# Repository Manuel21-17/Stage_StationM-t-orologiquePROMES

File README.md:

# Stage_StationM-t-orologiquePROMES
The following repository contains the various programs, CAD files, KiCad schematics, and applications developed as part of the project “CONCEPTION ET MISE EN SERVICE D’UNE PLATEFORME D’ADQUISITION DE DONNÉES MÉTÉOROLOGIQUES ET PHOTOVOLTAIQUES” during a 4-year internship as part of an engineering program.

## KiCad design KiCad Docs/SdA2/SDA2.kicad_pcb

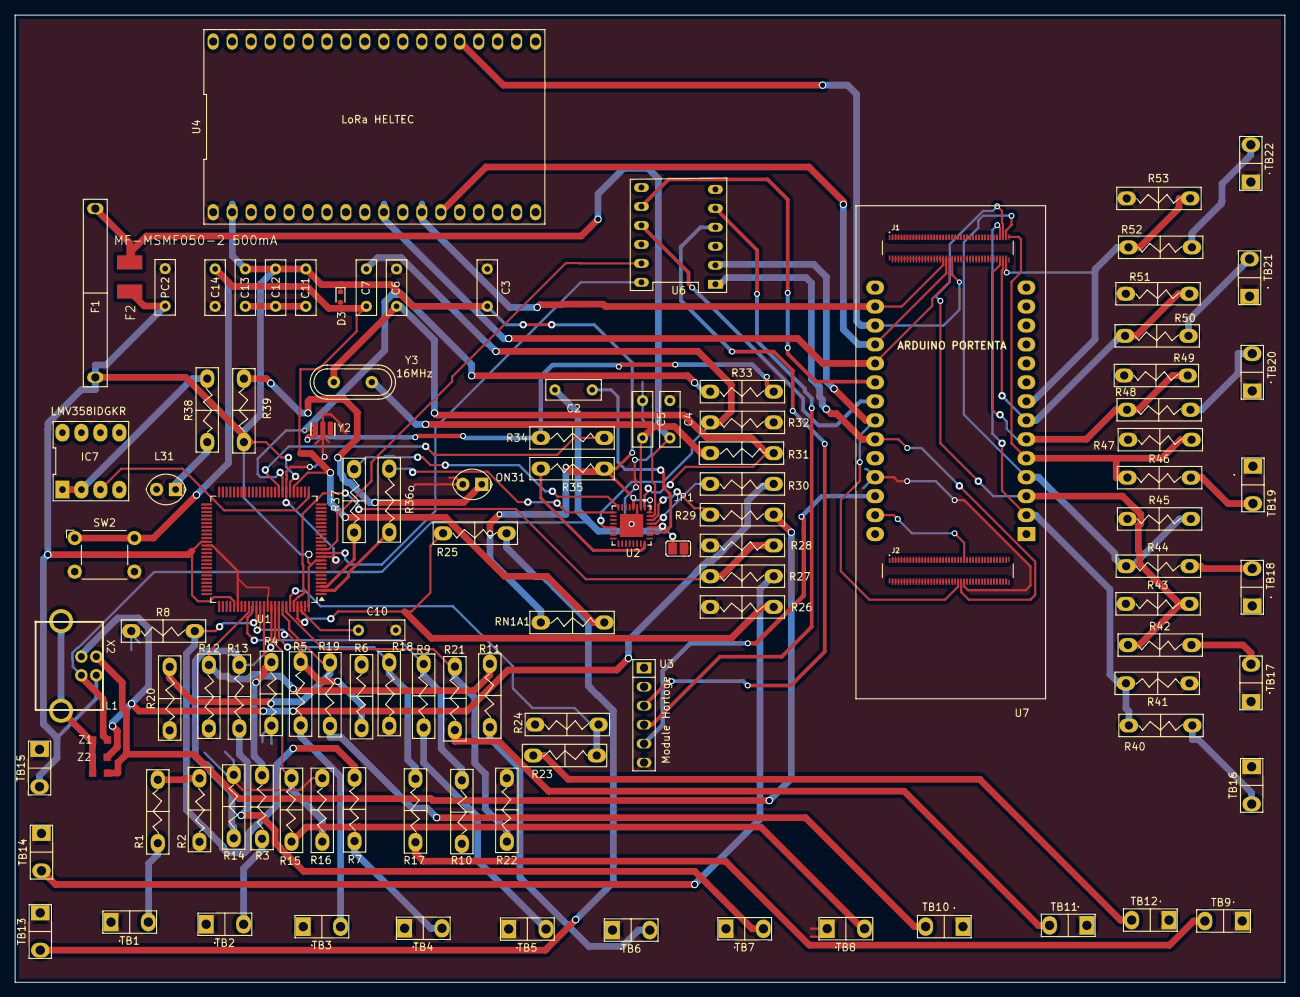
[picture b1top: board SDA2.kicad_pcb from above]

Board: 2 copper layers, 170.1 x 129.6 mm, 110 parts (0 on the bottom side), 81 nets.

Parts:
C2, C7: 1u; C_Rect_L7.2mm_W2.5mm_P5.00mm
C3, C4, C5, C6, C10, C11, C12, C13: 100n; C_Rect_L7.2mm_W2.5mm_P5.00mm
C14: 22p; C_Rect_L7.2mm_W2.5mm_P5.00mm
D3: 1N4148WT; D_SOD-523
F1: Fuse; Fussile
F2: MF-MSMF050-2 500mA; L1812
IC7: LMV358IDGKR; LM358N
J1, J2: DF40C-80DP-0.4V_51_; HRS_DF40C-80DP-0.4V_51_
JP1: SolderJumper_2_Open; OpenCircuit
L1: Z
L31: YELLOW; LED_Oval_W5.2mm_H3.8mm
ON31: GREEN; LED_Oval_W5.2mm_H3.8mm
PC2: 47u; C_Rect_L7.2mm_W2.5mm_P5.00mm
R1, R2, R3, R4, R5, R6, R7, R8, R9, R10, R11, R12, R13, R14, R15, R16, R17, R18, R19, R20, R21, R22, R23, R24, R25, R26, R27, R28, R29, R30, R31, R33, R34, R38, R39, R40, R41, R42, R43, R44, R45, R46, R47, R48, R49, R50, R51, R52, R53: R; RES
R32, R36, R37: 1K; RES
R35: 10k; RES
RN1A1: 10k; RES
SW2: SW_Omron_B3FS; SW_SPST_Omron_B3FS-100xP
TB1, TB2, TB3, TB4, TB5, TB6, TB7, TB8, TB9, TB10, TB11, TB12, TB13, TB14, TB15, TB16, TB17, TB18, TB19, TB20, TB21, TB22: TB2
U1: ATmega2560V-8A; TQFP-100_14x14mm_P0.5mm
U2: ATmega8U2-M; QFN-32-1EP_5x5mm_P0.5mm_EP3.1x3.1mm
U3: HORLOGE
U4: DIP-36_900_ELL
U6: Logic Shifter
U7: _REP_MODULE_ABX00042
X2: USB-B_TH; USB
Y2: 16MHz; HORLOGE1
Y3: CSTCE16; Horloge2
Z1, Z2: CG0603MLC-05E; Z

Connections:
+3.3V: U3.5 (VCC), U7.JD3 (+3.3)
+5V: C3.2, C11.1, C12.1, C13.1, D3.1 (K), F1.1, F2.2, PC2.1 (+), R35.2, R39.1, RN1A1.1, TB15.2, U1.10 (VCC), U1.31 (VCC), U1.61 (VCC), U1.80 (VCC), U1.100 (AVCC), U2.4 (VCC), U2.32 (AVCC), U4.2 (5V), U7.J1_32 (VIN), X2.1
/L13: IC7.1 (OUT), IC7.2 (-IN), R38.1
/PB7: IC7.3 (+IN), U1.26 (PB7)
CS_LORA: U4.12 (LoRa_CS), U7.J2_36 (D7)
EntCap1: R25.2, R26.1, U1.97 (PF0)
EntCap2: R27.2, R28.1, U1.96 (PF1)
GND: C3.1, C4.1, C5.1, C6.1, C10.2, C14.2, JP1.2 (B), L31.2, ON31.2, PC2.2 (-), R2.2, R4.2, R6.2, R8.2, R10.2, R12.2, R14.2, R16.2, R18.2, R20.2, R22.2, R24.2, R26.2, R28.2, R32.1, R41.2, R43.2, R45.2, R47.2, R49.2, R51.2, R53.2, SW2.2, TB1.1, TB2.1, TB3.1, TB4.1, TB5.1, TB6.1, TB7.1, TB8.1, TB9.1, TB10.1, TB11.1, TB12.1, TB13.1, TB14.1, TB15.1, TB16.1, TB17.1, TB18.1, TB19.1, TB20.1, TB21.1, TB22.1, U1.11 (GND), U1.32 (GND), U1.62 (GND), U1.81 (GND), U1.89 (PK0), U1.99 (GND), U2.3 (GND), U2.33 (GND), U3.6 (GND), U4.1 (GND), U7.J1_31 (GND), Y3.2
MISO: U4.10 (LoRa_MISO), U7.J2_40 (D10)
MOSI: U4.23 (LoRa_MOSI), U7.J2_42 (D8)
unnamed: C2.2, JP1.1 (A), L1.2, U2.28 (UGND), X2.4
unnamed: L1.1, X2.P$1, X2.P$2, Z1.1, Z2.1
unnamed: L31.1, R38.2
unnamed: ON31.1, R39.2
unnamed: R1.1, TB1.2
unnamed: R1.2, R2.1
unnamed: R3.1, TB2.2
unnamed: R5.1, TB3.2
unnamed: R7.1, TB4.2
unnamed: R9.1, TB5.2
unnamed: R11.1, TB6.2
unnamed: R13.1, TB7.2
unnamed: R15.1, TB8.2
unnamed: R17.1, TB9.2
unnamed: R19.1, TB10.2
unnamed: R21.1, TB11.2
unnamed: R23.1, TB12.2
unnamed: R25.1, TB13.2
unnamed: R27.1, TB14.2
unnamed: R29.1, X2.2, Z2.2
unnamed: R30.1, X2.3, Z1.2
unnamed: R33.1, R34.1, Y3.1
unnamed: R40.1, TB16.2
unnamed: R42.1, TB17.2
unnamed: R44.1, TB18.2
unnamed: R46.1, TB19.2
unnamed: R48.1, TB20.2
unnamed: R50.1, TB21.2
unnamed: R52.1, TB22.2
unnamed: C11.2, C12.2, C13.2
unnamed: C10.1, U1.98 (AREF)
unnamed: R23.2, R24.1, U1.95 (PF2)
unnamed: R21.2, R22.1, U1.94 (PF3)
unnamed: R19.2, R20.1, U1.93 (PF4)
unnamed: R17.2, R18.1, U1.92 (PF5)
unnamed: R15.2, R16.1, U1.91 (PF6)
unnamed: R13.2, R14.1, U1.90 (PF7)
unnamed: R3.2, R4.1, U1.88 (PK1)
unnamed: R5.2, R6.1, U1.87 (PK2)
unnamed: R7.2, R8.1, U1.86 (PK3)
unnamed: R9.2, R10.1, U1.85 (PK4)
unnamed: R11.2, R12.1, U1.84 (PK5)
unnamed: R34.2, U1.34 (XTAL1)
unnamed: R33.2, U1.33 (XTAL2), Y3.3
unnamed: R30.2, U2.29 (D+)
unnamed: R29.2, U2.30 (D-)
unnamed: C5.2, R31.1, U2.2 (PC0/XTAL2), Y2.1
unnamed: R35.1, U2.24 (PC1/~RESET)
unnamed: R37.1, U2.8 (PD2)
unnamed: R36.1, U2.9 (PD3)
unnamed: C2.1, U2.27 (UCAP)
unnamed: C4.2, F1.2, F2.1, U2.31 (UVCC)
unnamed: C6.2, R31.2, U2.1 (XTAL1), Y2.2
unnamed: C7.1, R32.2, U2.13 (~HWB/PD7)
unnamed: R40.2, R41.1, U7.J2_73 (A0)
unnamed: R42.2, R43.1, U7.J2_75 (A1)
unnamed: R44.2, R45.1, U7.J2_77 (A2)
unnamed: R46.2, R47.1, U7.J2_79 (A3)
unnamed: R48.2, R49.1, U7.J2_74 (A4)
unnamed: R50.2, R51.1, U7.J2_76 (A5/D20)
unnamed: R52.2, R53.1, U7.J2_78 (A6/D21)
PE0: R36.2, U1.2 (PE0)
PE1: R37.2, U1.3 (PE1)
PH0: U1.12 (PH0), U6.12 (HL1)
PH1: U1.13 (PH1), U6.11 (HL2)
RESET: C7.2, C14.1, D3.2 (A), RN1A1.2, SW2.1, U1.30 (~RESET)
RX_AP: U6.2 (LV2), U7.J1_35 (D13)
SCK: U4.13 (LoRa_SCLK), U7.J2_38 (D9)
SCLC: U3.3 (SCL), U7.J1_46 (D12)
SDAC: U3.4 (SDA), U7.J1_44 (D11)
TX_AP: U6.1 (LV1), U7.J1_33 (D14)

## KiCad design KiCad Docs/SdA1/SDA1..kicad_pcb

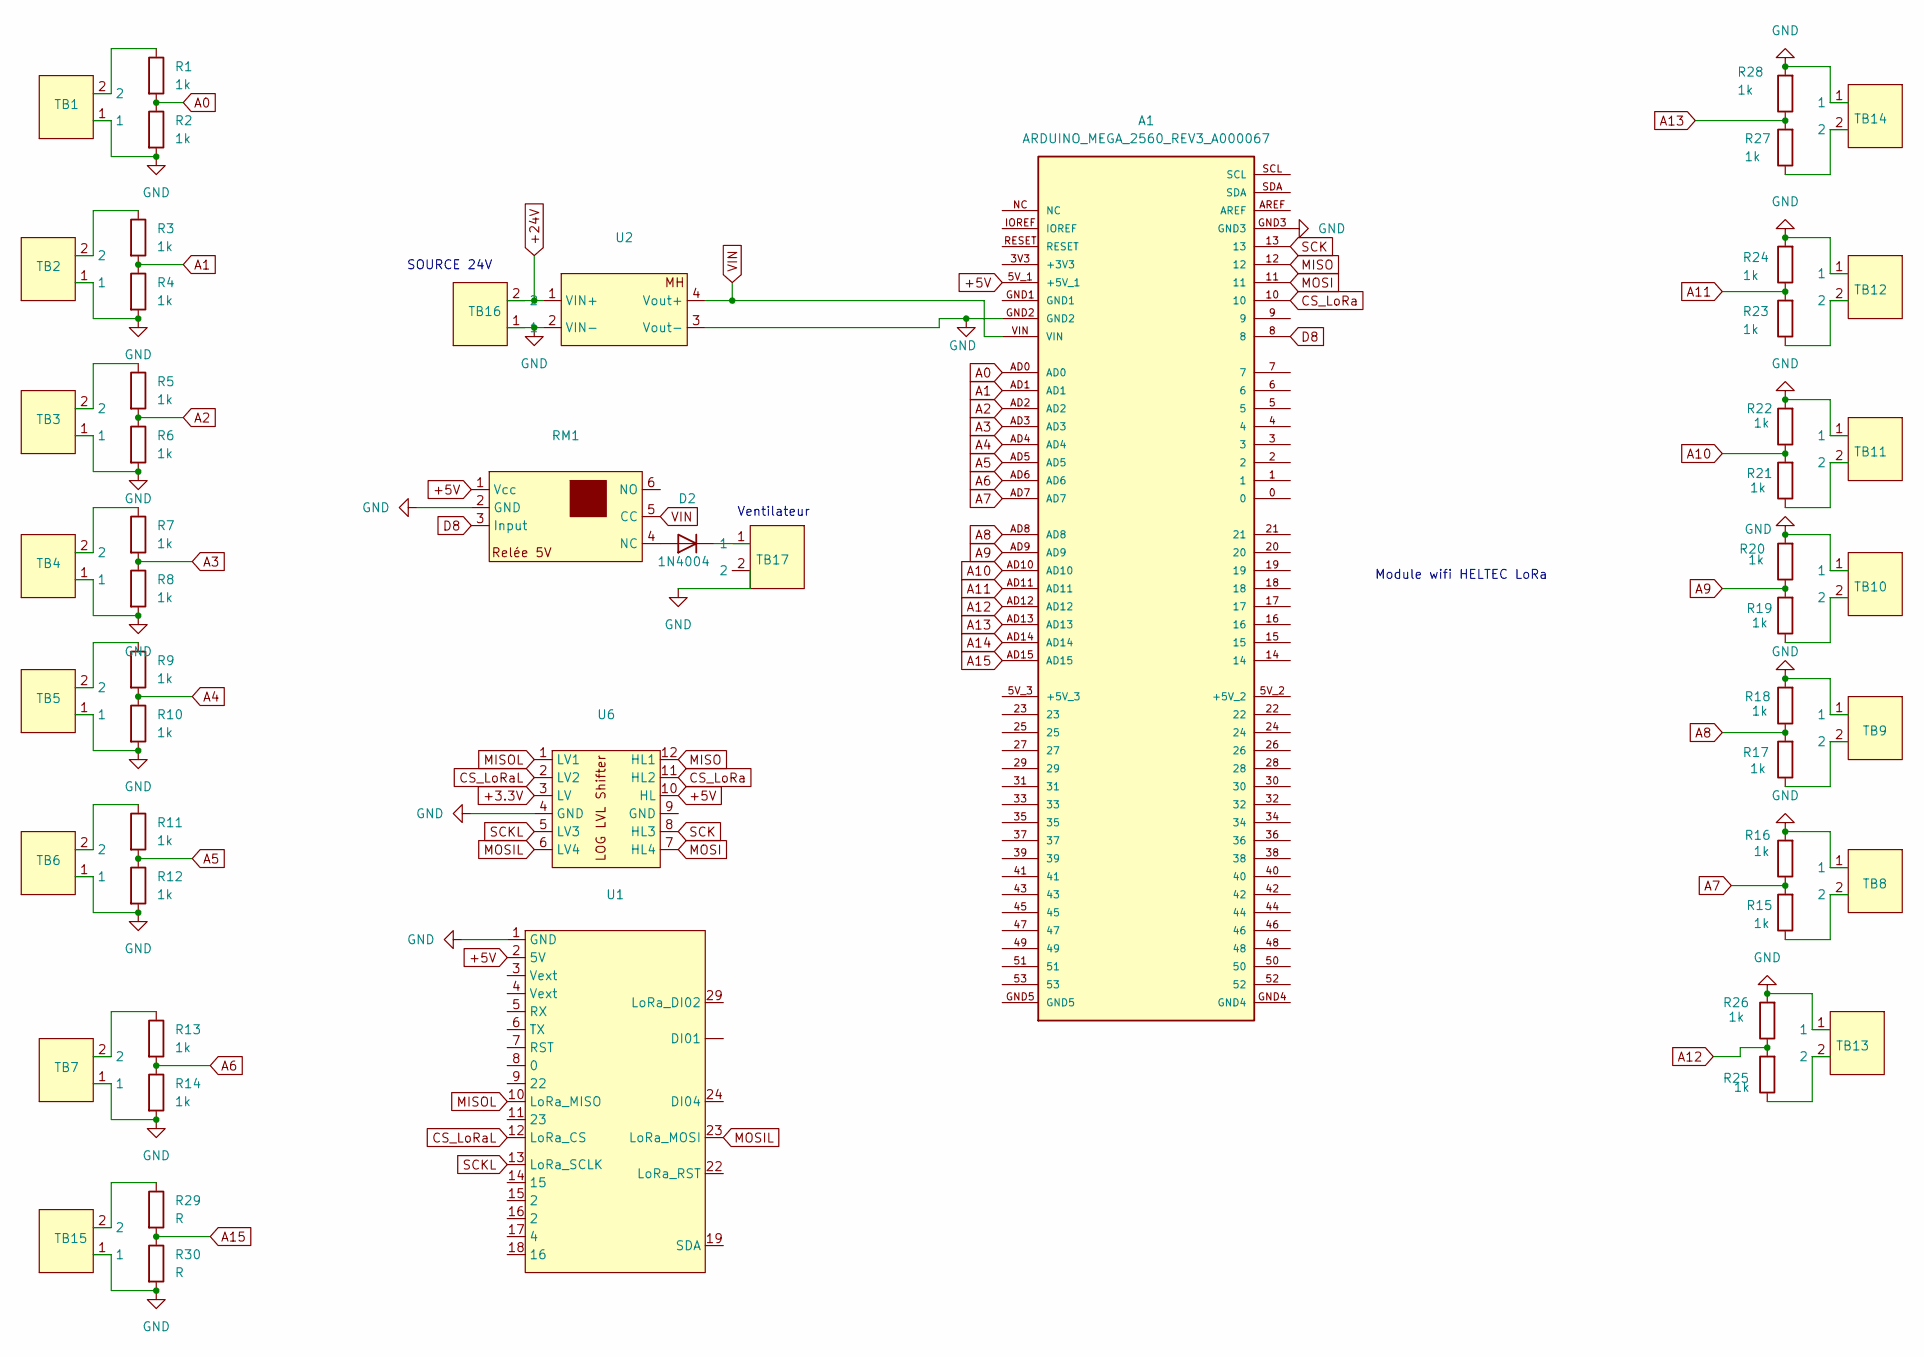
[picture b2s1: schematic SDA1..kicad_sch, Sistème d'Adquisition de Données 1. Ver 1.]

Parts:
A1: ARDUINO_MEGA_2560_REV3_A000067; ARDUINO_ARDUINO_MEGA_2560_REV3_A000067; PARTREV 3
D2: 1N4004; D_DO-41_SOD81_P10.16mm_Horizontal
R1, R2, R3, R4, R5, R6, R7, R8, R9, R10, R11, R12, R13, R14, R15, R16, R17, R18, R19, R20, R21, R22, R23, R24, R25, R26, R27, R28: 1k; RES
R29, R30: R; RES
RM1: RELÉE 5V
TB1, TB2, TB3, TB4, TB5, TB6, TB7, TB8, TB9, TB10, TB11, TB12, TB13, TB14, TB15, TB16, TB17: TB2
U1: DIP-36_900_ELL
U2: Regulateur de tension
U6: Logic Shifter

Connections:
+3.3V: U6.3 (LV)
+5V: A1.5V_1 (+5V_1), RM1.1 (Vcc), U1.2 (5V), U6.10 (HL)
+24V: TB16.2, U2.1 (VIN+)
A0: A1.AD0, R1.2, R2.1
A1: A1.AD1, R3.2, R4.1
A2: A1.AD2, R5.2, R6.1
A3: A1.AD3, R7.2, R8.1
A4: A1.AD4, R9.2, R10.1
A5: A1.AD5, R11.2, R12.1
A6: A1.AD6, R13.2, R14.1
A7: A1.AD7, R15.2, R16.1
A8: A1.AD8, R17.2, R18.1
A9: A1.AD9, R19.2, R20.1
A10: A1.AD10, R21.2, R22.1
A11: A1.AD11, R23.2, R24.1
A12: A1.AD12, R25.2, R26.1
A13: A1.AD13, R27.2, R28.1
A14: A1.AD14
A15: A1.AD15, R29.2, R30.1
CS_LoRa: A1.10, U6.11 (HL2)
CS_LoRaL: U1.12 (LoRa_CS), U6.2 (LV2)
D8: A1.8, RM1.3 (Input)
GND: A1.GND2, A1.GND3, R2.2, R4.2, R6.2, R8.2, R10.2, R12.2, R14.2, R16.2, R18.2, R20.2, R22.2, R24.2, R26.2, R28.2, R30.2, RM1.2 (GND), TB1.1, TB2.1, TB3.1, TB4.1, TB5.1, TB6.1, TB7.1, TB8.1, TB9.1, TB10.1, TB11.1, TB12.1, TB13.1, TB14.1, TB15.1, TB16.1, TB17.2, U1.1 (GND), U2.2 (VIN-), U2.3 (Vout-), U6.4 (GND)
MISO: A1.12, U6.12 (HL1)
MISOL: U1.10 (LoRa_MISO), U6.1 (LV1)
MOSI: A1.11, U6.7 (HL4)
MOSIL: U1.23 (LoRa_MOSI), U6.6 (LV4)
unnamed: D2.2 (A), RM1.4 (NC)
unnamed: D2.1 (K), TB17.1
unnamed: R1.1, TB1.2
unnamed: R3.1, TB2.2
unnamed: R5.1, TB3.2
unnamed: R7.1, TB4.2
unnamed: R9.1, TB5.2
unnamed: R11.1, TB6.2
unnamed: R13.1, TB7.2
unnamed: R15.1, TB8.2
unnamed: R17.1, TB9.2
unnamed: R19.1, TB10.2
unnamed: R21.1, TB11.2
unnamed: R23.1, TB12.2
unnamed: R25.1, TB13.2
unnamed: R27.1, TB14.2
unnamed: R29.1, TB15.2
SCK: A1.13, U6.8 (HL3)
SCKL: U1.13 (LoRa_SCLK), U6.5 (LV3)
VIN: A1.VIN, RM1.5 (CC), U2.4 (Vout+)

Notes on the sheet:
Ventilateur
SOURCE 24V
Module wifi HELTEC LoRa

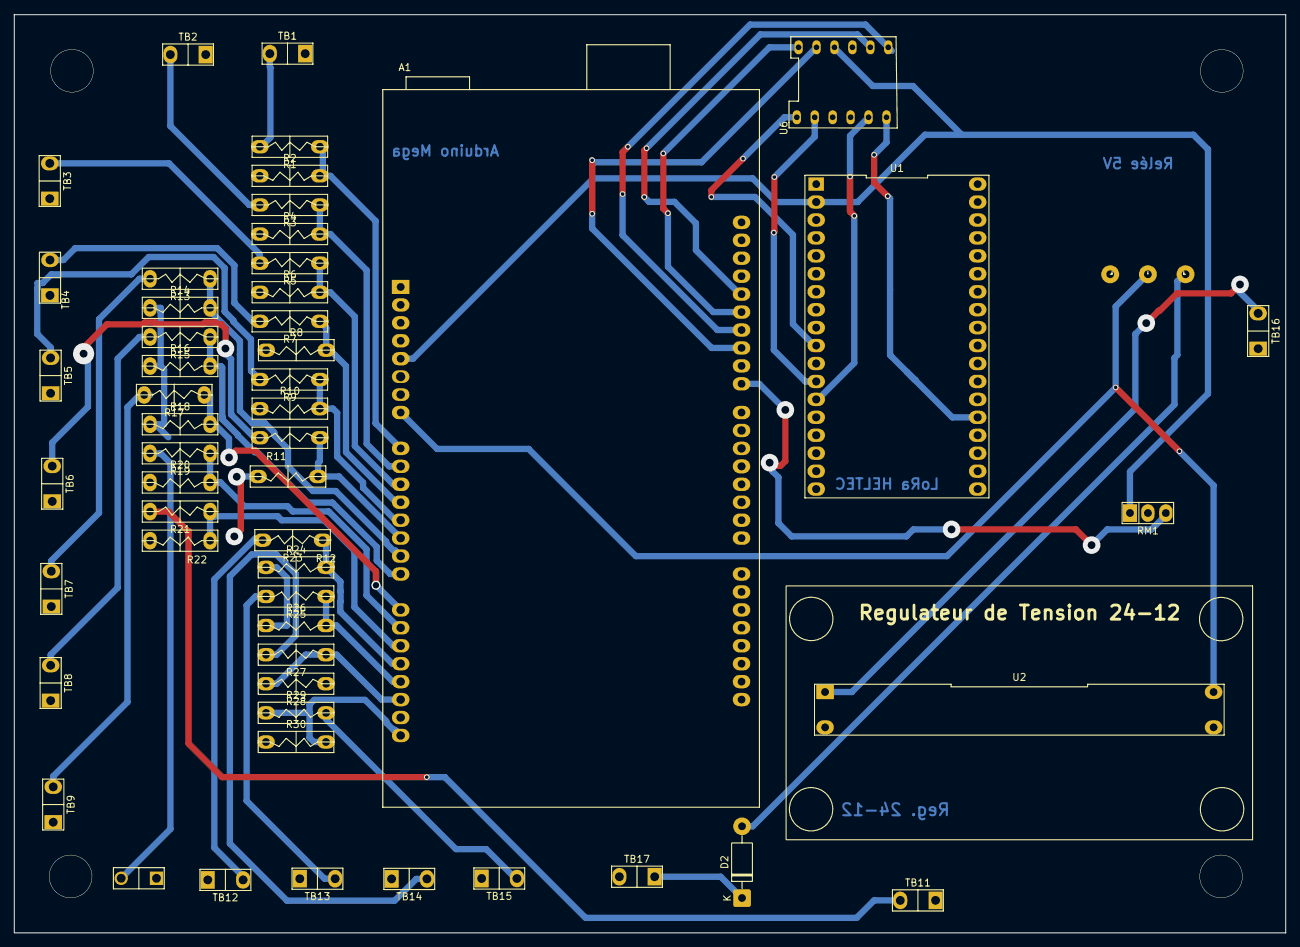
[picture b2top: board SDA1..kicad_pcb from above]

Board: 2 copper layers, 180.0 x 130.0 mm, 53 parts (0 on the bottom side), 45 nets.
